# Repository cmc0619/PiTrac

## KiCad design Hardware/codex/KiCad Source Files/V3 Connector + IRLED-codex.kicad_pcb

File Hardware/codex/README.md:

# V3 hardware: Codex variant

This revision starts from PiTracLM/PiTrac `78f1de60fd21398f34d348f19f55e73029bc95f9` and makes three physical corrections. It retains the original architecture and populated parts except for R5's resistance value.

| Change | Reason and effect |
| --- | --- |
| R5: 2.49 kOhm to 6.8 kOhm, `MFR-25FTE52-6K8` | The green supply indicator's original 0.25 W resistor dissipates approximately 0.450 W at the nominal 35.57 V rail. The replacement dissipates approximately 0.165 W and reduces rail load by about 0.303 W. The green indicator is dimmer; the IR LED current-setting network is unchanged. |
| J2/J5 USB4085 power-contact copper | The original front/inner copper diameter was 0.10 mm around a 0.40 mm plated drill. The corrected 0.68 mm land gives a nominal 0.14 mm annular ring. Bottom solder lands are extended to surround the same drills; the local thermal gap is 0.20 mm. |
| D6-D15 center anode connections | The VSMA1085400 center contact is an anode. It is now connected to each LED's existing anode net with a 2.8 x 0.4 mm copper bridge. The bridge stays under solder mask; existing paste and mask openings are unchanged. |

Every existing component position and orientation, mounting hole, drilled pad, via, outline, and 3D model placement is preserved. Existing cases and printed-part geometry are unchanged. Software, the DAC setting/scale, boost current-limit resistor, LED current-setting network and pulse timing are unchanged. No new fuse, TVS, pulse limiter, or USB power-delivery controller is added.

Project-local library tables and project-specific transistor/LED symbols preserve the actual upstream pin definitions when the project is opened on another computer. Intentional unconnected pins, power sources and breakaway holes are identified explicitly. The connector-only board now has its own project file with the same fabrication rules as the combined board.

This directory contains the separately named `-codex` variant. The existing hardware files elsewhere under `Hardware/` remain the Claude/main variant, unchanged. Open `KiCad Source Files/V3 Connector + IRLED-codex.kicad_pro` for this design. The connector-only and LED-only projects are PCB variants; the combined project contains the complete schematic.

## Files to use

- `KiCad Source Files/`: native KiCad 9 schematics, project files, boards and local libraries. KiCad 10 can also read/check these files.
- `Fabrication Files/`: regenerated Gerber and separate plated/nonplated drill ZIPs for all three board variants. Export filenames retain `IRLED2` where applicable and append `-codex`. Internal fabrication filenames use the suffixed PCB project names.
- `Assembly Files/`: regenerated BOMs and centroids. Reference sets and placement coordinates are unchanged; R5 is the only changed ordered part.
- `Schematic/V3 Connector + IRLED2 Schematic-codex.pdf`: regenerated complete schematic.
- `Validation/upstream-iteration/`: verification summary and focused resistor calculation/SPICE evidence.

U4 and C13 remain **do not populate**, as in upstream. They are omitted from the assembly files. With U4 absent, R11 already pulls the MCP4801 shutdown pin high; no DAC modification is needed.

Custom libraries use the `Pi Connector Parts-codex` namespace. The corrected USB4085 and VSMA1085400 footprints also have `-codex` item names. Manufacturer part numbers, schematic values and reference designators are unchanged by naming.

## Verification

KiCad 9.0.8 checks all three boards with zero DRC errors and zero unconnected copper items. The full schematic has zero active ERC violations and two documented, narrowly scoped exceptions: the MC33063 switch emitter tied to ground and the MCP1407's internally connected output pins tied together. No global rule severities were relaxed.

KiCad 10.0.6 independently checks the combined board and full schematic with the same zero-error result. Residual warnings are reported explicitly:

- Each connector board has 16 footprint-library mismatch warnings: 14 standard-footprint differences and two USB instance/library differences. The LED-only board has none.
- Combined-board schematic parity reports 18 unused USB signal pins without copper pads. These dedicated power-only footprints retain those unused contacts as unplated holes, as upstream.
- KiCad 10 additionally reports 32 legacy empty-versus-`~` Datasheet-field differences. These do not change components or connections.

Independent checks compare the original and final netlists, native pad assignments, tracks/vias, holes, outlines, component placements, DNP flags and assembly data. Original pin connectivity is unchanged apart from the ten intended center-anode additions. A separate reviewer found no material introduced defect in the reviewed design at `269b162`. `Validation/naming-codex.json` records the subsequent naming-only checks. The evidence in `Validation/upstream-iteration/` retains its original pre-rename filenames and provenance.

The focused ngspice calculation models only the indicator branch, using a nominal 2.1 V LED drop. Its results agree with resistor-power arithmetic. A conservative 38 V/zero-LED-drop bound including resistor tolerance and temperature coefficient gives approximately 0.215 W for the replacement, below its 0.25 W rating through 70 C local ambient. Higher-temperature operation requires the manufacturer's derating curve and actual conditions.

## Boundaries

These checks establish CAD consistency and the stated electrical calculations. They do not establish measured light output, enclosure temperature, solder yield or physical fit of a populated assembly.

The existing MC33063 charging-current limit remains a separate issue: its 0.15 Ohm sense resistor implies a nominal 2 A threshold, above the controller's 1.5 A switch rating. A lower limit changes reservoir recharge; this revision does not claim to resolve it while preserving the complete strobe/calibration operating envelope. The actual calibration pulse includes software/SPI overhead, so its duration cannot be inferred solely from the SPI wire time.

J2/J5 remain dedicated Pi5 power outputs without USB PD negotiation. Adding ordinary Type-C source resistors would not establish 5 A PD capability. The existing Pi5 supply configuration and upstream current requirements still apply.

## Manufacturer references

- [Yageo MFR resistor ratings, dimensions and ordering](https://yageogroup.com/content/Resource%20Library/Datasheet/YAGEO-MFR_DATASHEET.pdf)
- [Vishay VSMA1085400 package and recommended copper, page 6](https://www.vishay.com/docs/80294/vsma1085400.pdf)
- [GCT USB4085 connector](https://gct.co/connector/usb4085)
- [TI MC33063A controller](https://www.ti.com/lit/ds/symlink/mc33063a.pdf)
- [Microchip MCP1406/1407 output-pin description](https://ww1.microchip.com/downloads/en/DeviceDoc/20002019C.pdf)
- [Raspberry Pi 5 USB Power Delivery](https://pip-assets.raspberrypi.com/categories/685-app-notes-guides-whitepapers/documents/RP-009856-WP-1-USB%20Power%20delivery%20on%20Raspberry%20Pi%205.pdf)

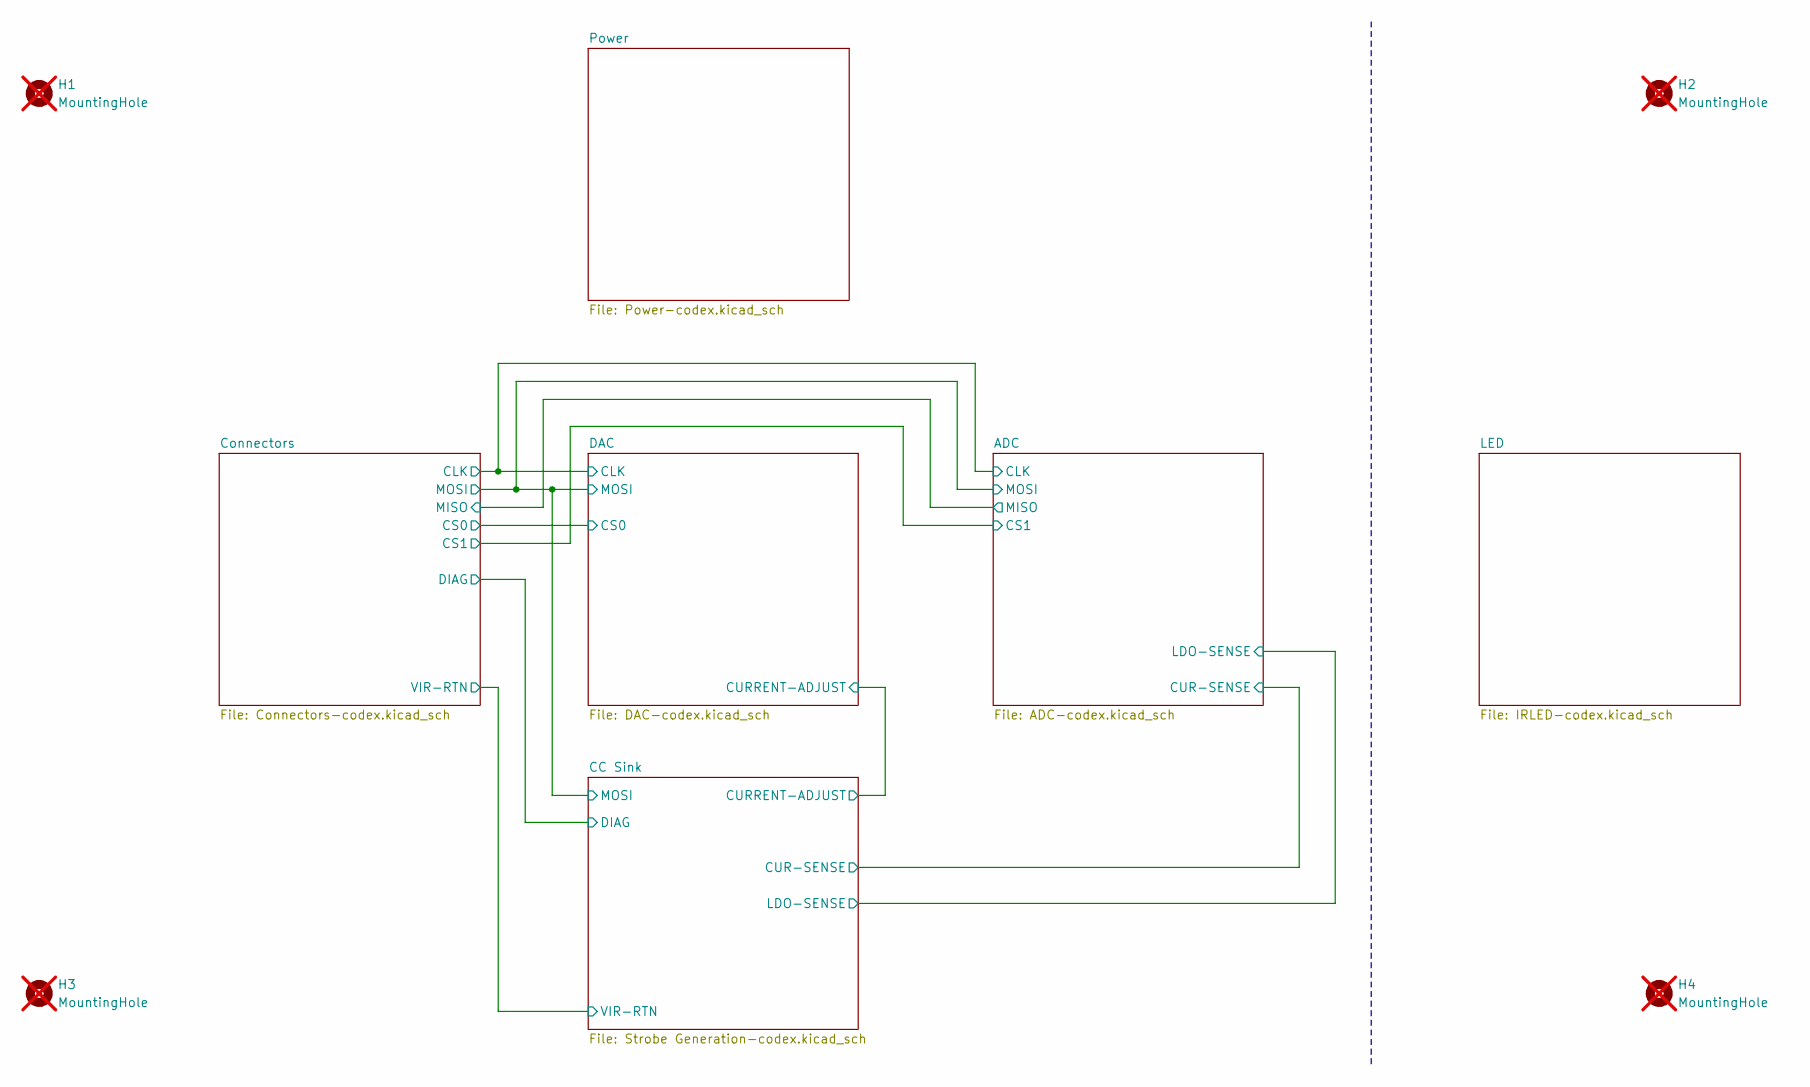
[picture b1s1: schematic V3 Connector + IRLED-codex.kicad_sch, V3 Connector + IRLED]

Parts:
H1, H2, H3, H4: MountingHole; MountingHole_3.5mm; not fitted

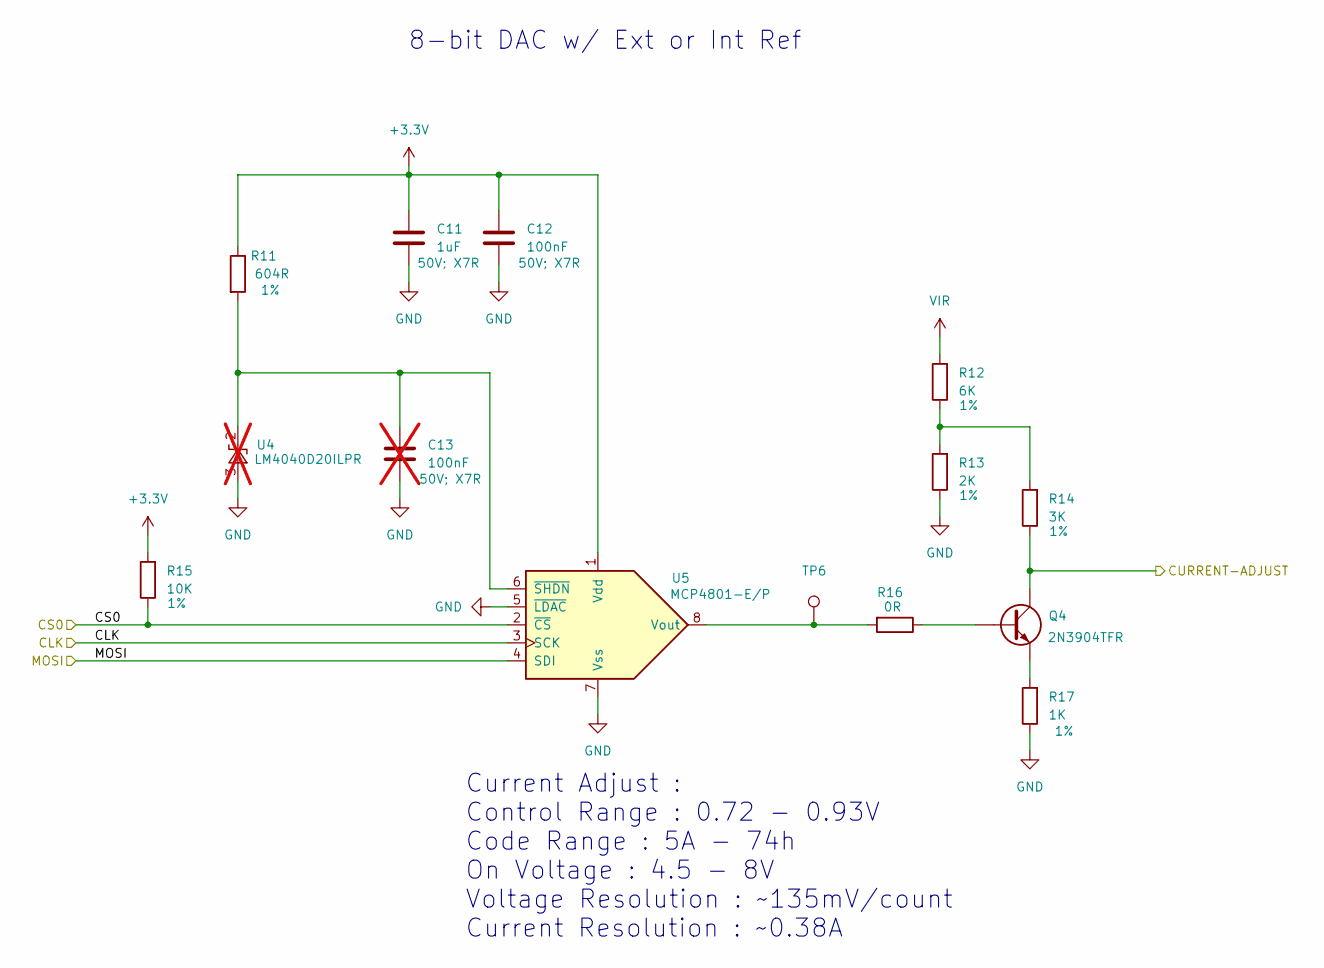
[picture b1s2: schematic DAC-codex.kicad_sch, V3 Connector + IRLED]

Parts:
C11: 1uF; C_Disc_D5.1mm_W3.2mm_P5.00mm; Ratings 50V; X7R; Part Number K105K20X7RF5TH5
C12: 100nF; C_Disc_D4.3mm_W1.9mm_P5.00mm; Ratings 50V; X7R; Part Number K104K10X7RF5UH5
C13: 100nF; C_Disc_D4.3mm_W1.9mm_P5.00mm; Ratings 50V; X7R; Part Number K104K10X7RF5UH5; not fitted
Q4: TO-92_Inline_Wide; Part Number 2N3904TFR
R11: 604R; R_Axial_DIN0207_L6.3mm_D2.5mm_P7.62mm_Horizontal; Ratings 1%; Part Number MFR-25FRF52-604R
R12: 6K; R_Axial_DIN0207_L6.3mm_D2.5mm_P7.62mm_Horizontal; Ratings 1%; Part Number MFR-25FBF52-6K04
R13: 2K; R_Axial_DIN0207_L6.3mm_D2.5mm_P7.62mm_Horizontal; Ratings 1%; Part Number MFR-25FRF52-2K
R14: 3K; R_Axial_DIN0207_L6.3mm_D2.5mm_P7.62mm_Horizontal; Ratings 1%; Part Number MFR-25FRF52-3K
R15: 10K; R_Axial_DIN0207_L6.3mm_D2.5mm_P15.24mm_Horizontal; Ratings 1%; Part Number MFR-25FRF52-10K
R16: 0R; R_Axial_DIN0207_L6.3mm_D2.5mm_P7.62mm_Horizontal; Part Number ZOR-25-R-52-0R
R17: 1K; R_Axial_DIN0207_L6.3mm_D2.5mm_P7.62mm_Horizontal; Ratings 1%; Part Number MFR-25FRF52-1K
TP6: TestPoint; TestPoint_Pad_D1.0mm
U4: LM4040LP-2.0; TO-92_Inline_Wide; Part Number LM4040D20ILPR; not fitted
U5: MCP4801; DIP-8_W7.62mm; Part Number MCP4801-E/P

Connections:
+3.3V: C11.1, C12.1, R11.1, R15.2, U5.1 (Vdd); also elsewhere on the board
/ADC/CLK: U5.3 (SCK); also elsewhere on the board
/ADC/MOSI: U5.4 (SDI); also elsewhere on the board
/CC Sink/CURRENT-ADJUST: Q4.3 (C), R14.1; also elsewhere on the board
/Connectors/CS0: R15.1, U5.2 (~CS); also elsewhere on the board
GND: C11.2, C12.2, C13.2, R13.1, R17.1, U4.3 (A), U5.5 (~LDAC), U5.7 (Vss); also elsewhere on the board
unnamed: Q4.2 (B), R16.1
unnamed: Q4.1 (E), R17.2
unnamed: R12.1, R13.2, R14.2
unnamed: C13.1, R11.2, U4.2 (K), U5.6 (~SHDN)
unnamed: R16.2, TP6.1, U5.8 (Vout)
VIR: R12.2; also elsewhere on the board

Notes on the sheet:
Current Adjust : Control Range : 0.72 - 0.93V Code Range : 5A - 74h On Voltage : 4.5 - 8V Voltage Resolution : ~135mV/count Current Resolution : ~0.38A
8-bit DAC w/ Ext or Int Ref

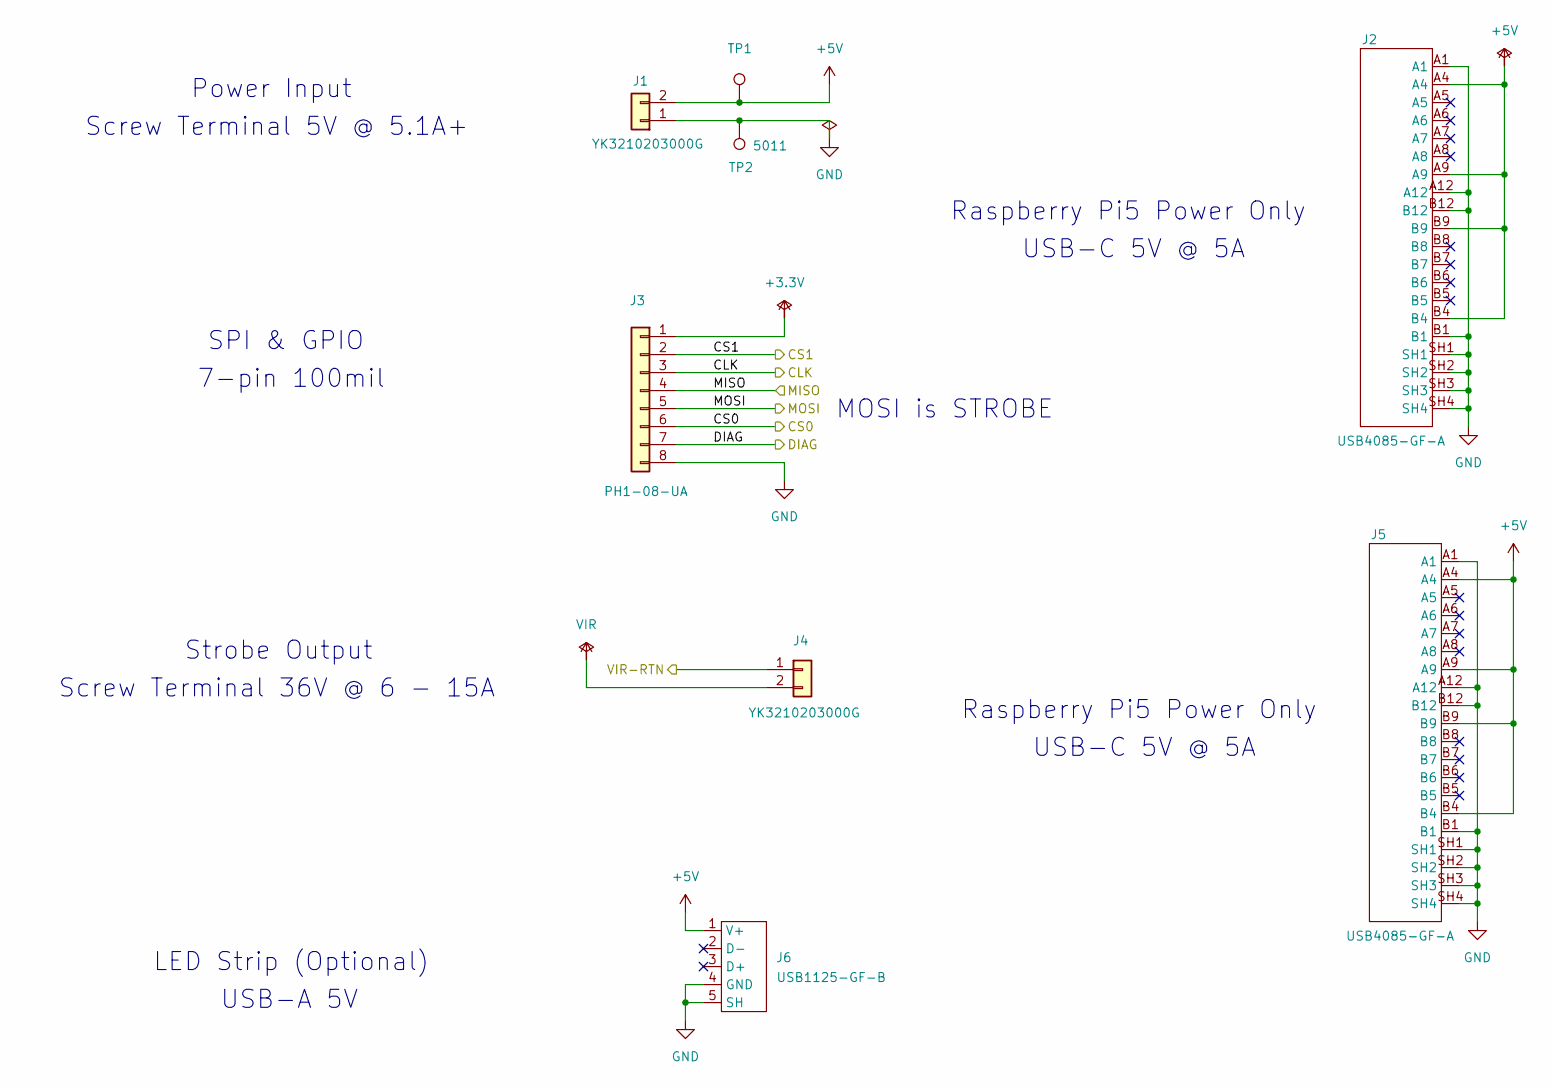
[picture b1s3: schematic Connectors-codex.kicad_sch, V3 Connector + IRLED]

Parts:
J1, J4: YK3210203000G; Part Number YK3210203000G
J2, J5: USB4085-GF-A; USB4085-GF-A-codex; Part Number USB4085-GF-A
J3: Conn_01x08; PinHeader_1x08_P2.54mm_Vertical; Part Number PH1-08-UA
J6: USB1125-GF-B; Part Number USB1125-GF-B
TP1: TestPoint; TestPoint_Pad_D1.0mm
TP2: TestPoint; TestPoint_Keystone_5010-5014_Multipurpose; Part Number 5011

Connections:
+3.3V: J3.1; also elsewhere on the board
+5V: J1.2, J2.A4, J2.A9, J2.B4, J2.B9, J5.A4, J5.A9, J5.B4, J5.B9, J6.1 (V+), TP1.1; also elsewhere on the board
/ADC/CLK: J3.3; also elsewhere on the board
/ADC/CS1: J3.2; also elsewhere on the board
/ADC/MISO: J3.4; also elsewhere on the board
/ADC/MOSI: J3.5; also elsewhere on the board
/CC Sink/DIAG: J3.7; also elsewhere on the board
/CC Sink/VIR-RTN: J4.1; also elsewhere on the board
/Connectors/CS0: J3.6; also elsewhere on the board
GND: J1.1, J2.A1, J2.A12, J2.B1, J2.B12, J2.SH1, J2.SH2, J2.SH3, J2.SH4, J3.8, J5.A1, J5.A12, J5.B1, J5.B12, J5.SH1, J5.SH2, J5.SH3, J5.SH4, J6.4 (GND), J6.5 (SH), TP2.1; also elsewhere on the board
VIR: J4.2; also elsewhere on the board

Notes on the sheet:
Power Input
Raspberry Pi5 Power Only
LED Strip (Optional)
Screw Terminal 36V @ 6 - 15A
MOSI is STROBE
7-pin 100mil
USB-C 5V @ 5A
Screw Terminal 5V @ 5.1A+
USB-A 5V
Strobe Output
SPI & GPIO

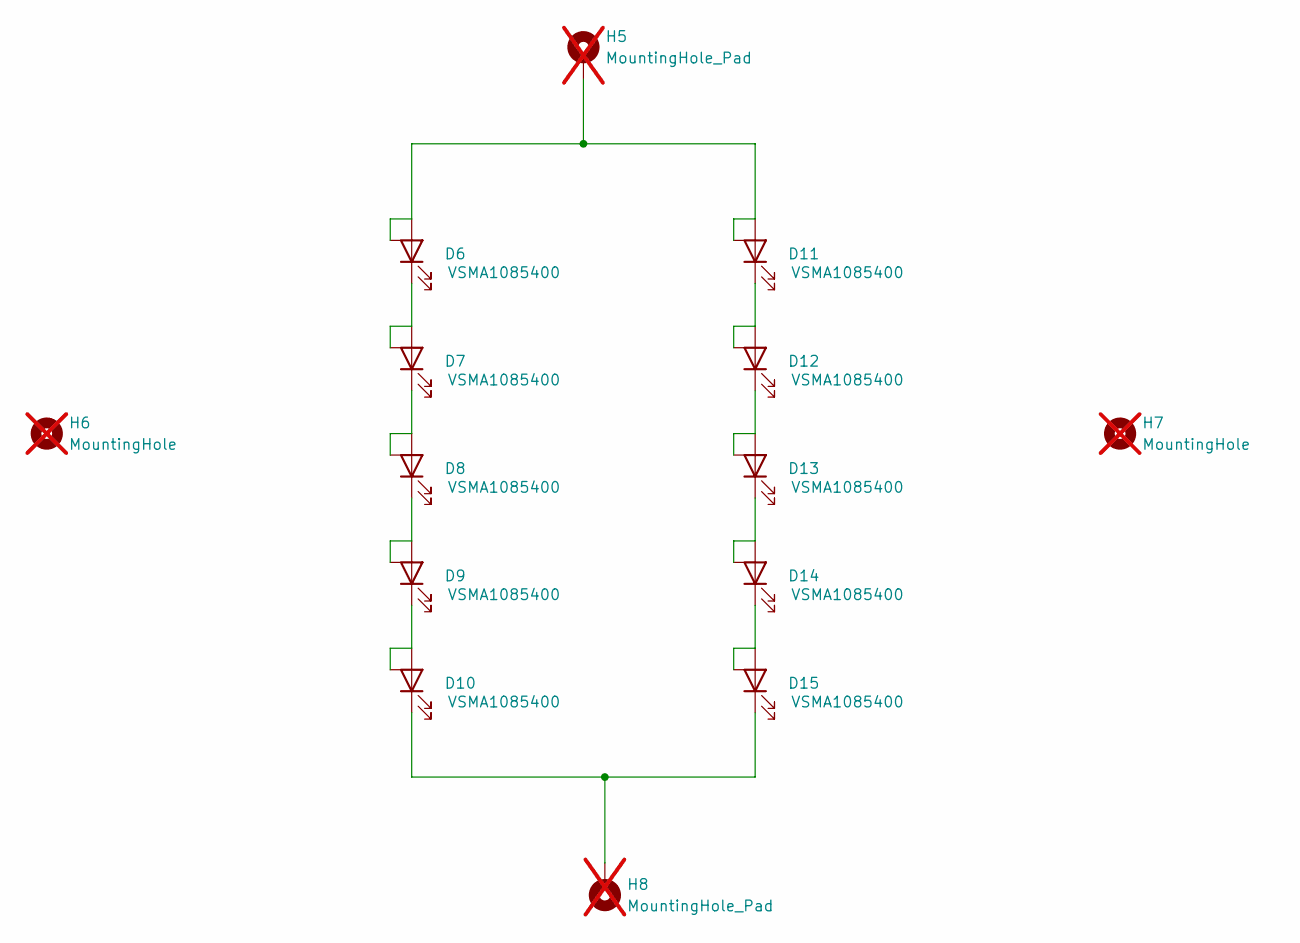
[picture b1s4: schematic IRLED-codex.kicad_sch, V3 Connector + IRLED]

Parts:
D6, D7, D8, D9, D10, D11, D12, D13, D14, D15: VSMA1085400; VSMA1085400-codex; Part Number VSMA1085400
H5, H8: MountingHole_Pad; MountingHole_2.2mm_M2_Pad; not fitted
H6, H7: MountingHole; MountingHole_3.2mm_M3; not fitted

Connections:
unnamed: D6.1 (K), D7.2 (A), D7.3
unnamed: D7.1 (K), D8.2 (A), D8.3
unnamed: D8.1 (K), D9.2 (A), D9.3
unnamed: D9.1 (K), D10.2 (A), D10.3
unnamed: D10.1 (K), D15.1 (K), H8.1
unnamed: D6.2 (A), D6.3, D11.2 (A), D11.3, H5.1
unnamed: D11.1 (K), D12.2 (A), D12.3
unnamed: D12.1 (K), D13.2 (A), D13.3
unnamed: D13.1 (K), D14.2 (A), D14.3
unnamed: D14.1 (K), D15.2 (A), D15.3

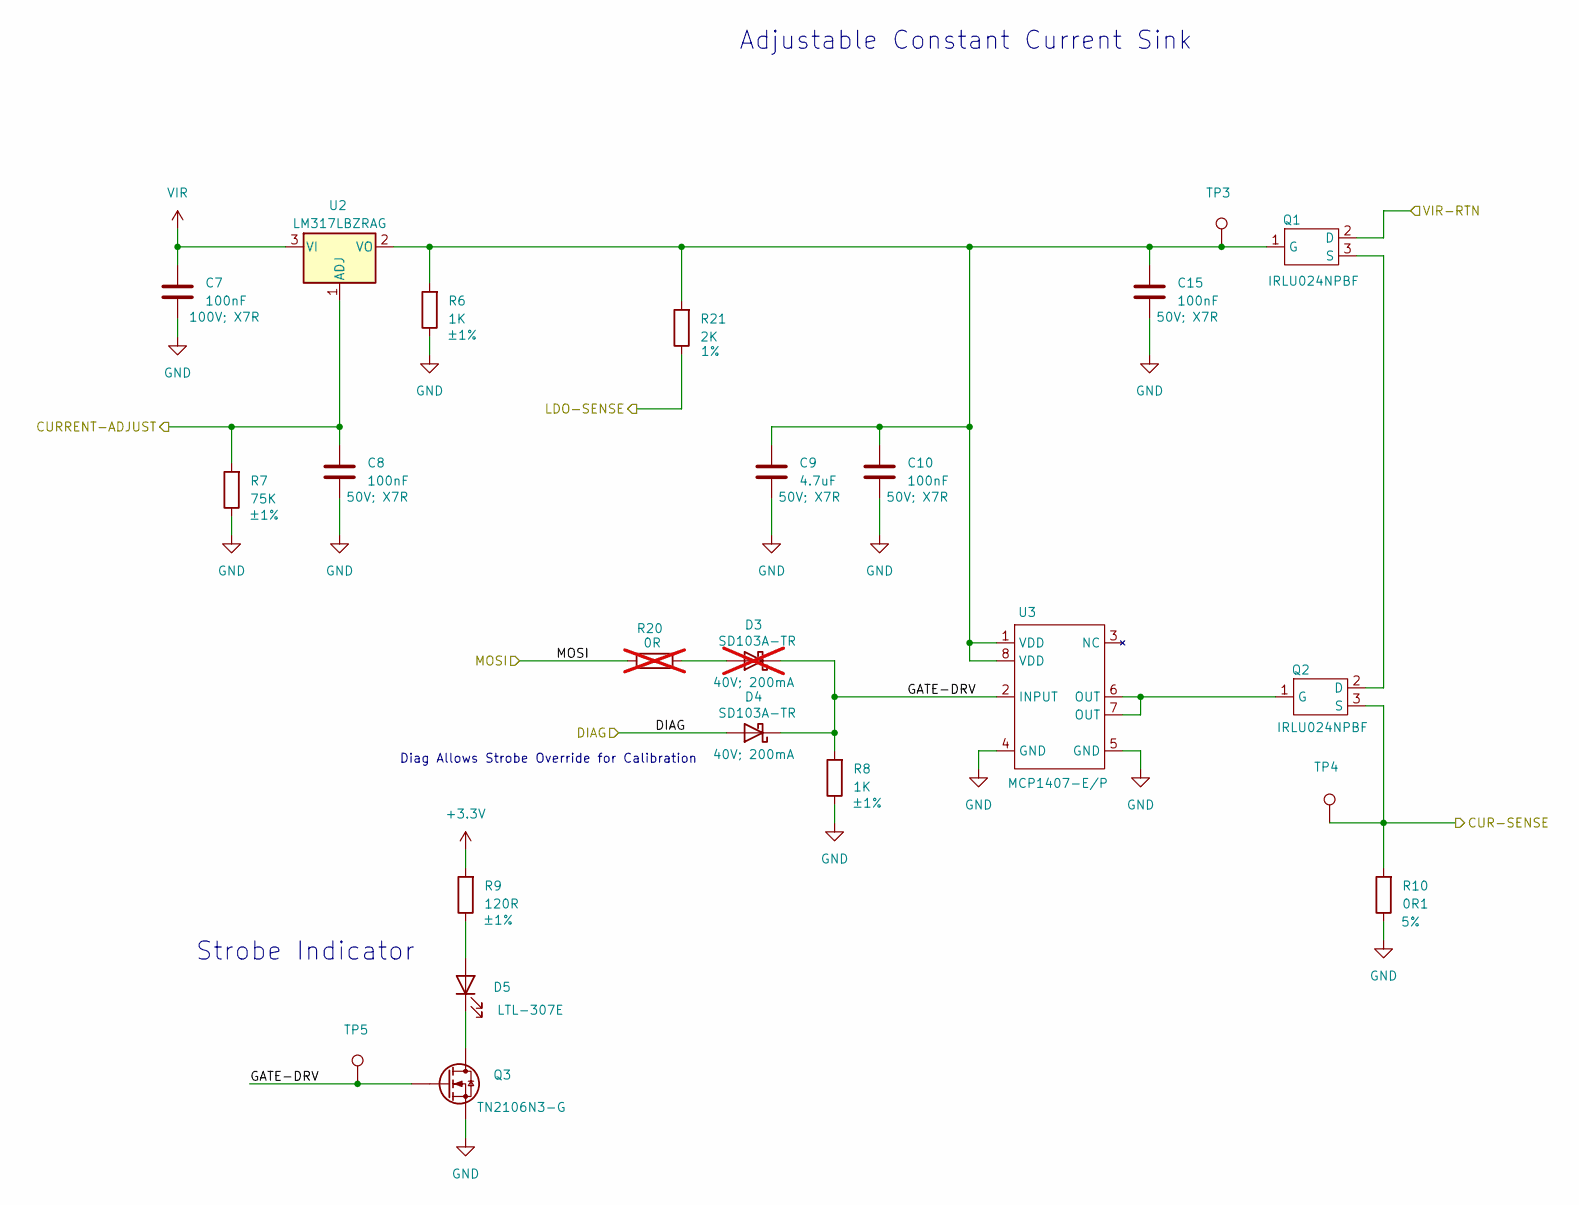
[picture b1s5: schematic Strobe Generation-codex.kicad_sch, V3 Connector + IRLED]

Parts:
C7: 100nF; C_Disc_D5.1mm_W3.2mm_P5.00mm; Ratings 100V; X7R; Part Number K104K20X7RH5UH5
C8, C10, C15: 100nF; C_Disc_D4.3mm_W1.9mm_P5.00mm; Ratings 50V; X7R; Part Number K104K10X7RF5UH5
C9: 4.7uF; C_Disc_D6.0mm_W4.4mm_P5.00mm; Ratings 50V; X7R; Part Number RCER71H475K3K1H03B
D3: D_Schottky; D_DO-35_SOD27_P7.62mm_Horizontal; Ratings 40V; 200mA; Part Number SD103A-TR; not fitted
D4: D_Schottky; D_DO-35_SOD27_P7.62mm_Horizontal; Ratings 40V; 200mA; Part Number SD103A-TR
D5: LTL-307E; LED_D5.0mm; Part Number LTL-307E
Q1, Q2: IRLU024NPBF; TO-251-3_Vertical; Part Number IRLU024NPBF
Q3: Q_NMOS; TO-92_Inline_Wide; Part Number TN2106N3-G
R6, R8: 1K; R_Axial_DIN0207_L6.3mm_D2.5mm_P7.62mm_Horizontal; Ratings ±1%; Part Number MFR-25FRF52-1K
R7: 75K; R_Axial_DIN0207_L6.3mm_D2.5mm_P7.62mm_Horizontal; Ratings ±1%; Part Number MFR-25FRF52-75K
R9: 120R; R_Axial_DIN0207_L6.3mm_D2.5mm_P7.62mm_Horizontal; Ratings ±1%; Part Number MFR-25FTE52-120R
R10: 0R1; R_Axial_DIN0414_L11.9mm_D4.5mm_P15.24mm_Horizontal; Ratings 5%; Part Number KNP100JR-73-0R1
R20: 0R; R_Axial_DIN0207_L6.3mm_D2.5mm_P7.62mm_Horizontal; Part Number ZOR-25-R-52-0R; not fitted
R21: 2K; R_Axial_DIN0207_L6.3mm_D2.5mm_P7.62mm_Horizontal; Ratings 1%; Part Number MFR-25FRF52-2K
TP3, TP4, TP5: TestPoint; TestPoint_Pad_D1.0mm
U2: TO-92_Inline_Wide; Part Number LM317LBZRAG
U3: DIP-8_W7.62mm; Part Number MCP1407-E/P

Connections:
+3.3V: R9.2; also elsewhere on the board
/ADC/CUR-SENSE: Q2.3 (S), R10.2, TP4.1; also elsewhere on the board
/ADC/LDO-SENSE: R21.1; also elsewhere on the board
/ADC/MOSI: R20.2; also elsewhere on the board
/CC Sink/CURRENT-ADJUST: C8.1, R7.2, U2.1 (ADJ); also elsewhere on the board
/CC Sink/DIAG: D4.2 (A); also elsewhere on the board
/CC Sink/GATE-DRV: D3.1 (K), D4.1 (K), Q3.2, R8.2, TP5.1, U3.2 (INPUT)
/CC Sink/VIR-RTN: Q1.2 (D); also elsewhere on the board
GND: C7.2, C8.2, C9.2, C10.2, C15.2, Q3.1, R6.1, R7.1, R8.1, R10.1, U3.4 (GND), U3.5 (GND); also elsewhere on the board
unnamed: D3.2 (A), R20.1
unnamed: D5.2 (A), R9.1
unnamed: D5.1 (K), Q3.3
unnamed: C9.1, C10.1, C15.1, Q1.1 (G), R6.2, R21.2, TP3.1, U2.2 (VO), U3.1 (VDD), U3.8 (VDD)
unnamed: Q1.3 (S), Q2.2 (D)
unnamed: Q2.1 (G), U3.6 (OUT), U3.7 (OUT)
VIR: C7.1, U2.3 (VI); also elsewhere on the board

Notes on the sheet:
Diag Allows Strobe Override for Calibration
Adjustable Constant Current Sink
Strobe Indicator

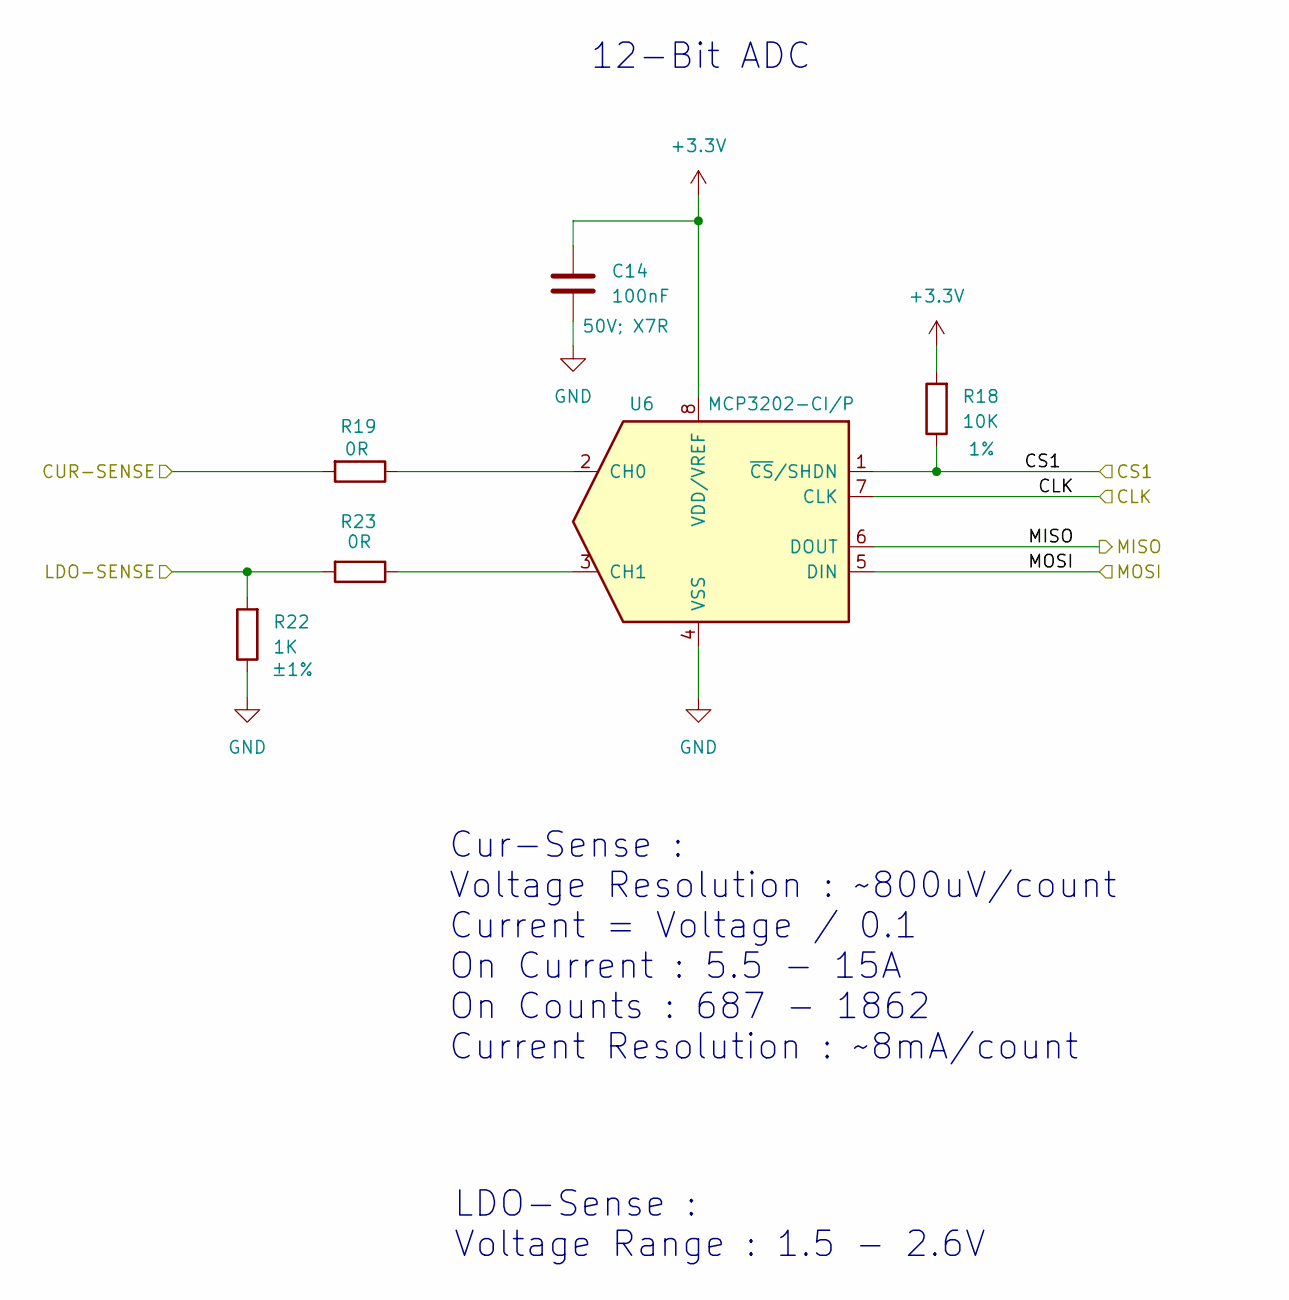
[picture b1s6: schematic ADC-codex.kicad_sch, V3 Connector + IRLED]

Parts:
C14: 100nF; C_Disc_D4.3mm_W1.9mm_P5.00mm; Ratings 50V; X7R; Part Number K104K10X7RF5UH5
R18: 10K; R_Axial_DIN0207_L6.3mm_D2.5mm_P7.62mm_Horizontal; Ratings 1%; Part Number MFR-25FRF52-10K
R19, R23: 0R; R_Axial_DIN0207_L6.3mm_D2.5mm_P15.24mm_Horizontal; Part Number ZOR-25-R-52-0R
R22: 1K; R_Axial_DIN0207_L6.3mm_D2.5mm_P7.62mm_Horizontal; Ratings ±1%; Part Number MFR-25FRF52-1K
U6: MCP3202; DIP-8_W7.62mm; Part Number MCP3202-CI/P

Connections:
+3.3V: C14.1, R18.2, U6.8 (VDD/VREF); also elsewhere on the board
/ADC/CLK: U6.7 (CLK); also elsewhere on the board
/ADC/CS1: R18.1, U6.1 (~CS/SHDN); also elsewhere on the board
/ADC/CUR-SENSE: R19.2; also elsewhere on the board
/ADC/LDO-SENSE: R22.2, R23.2; also elsewhere on the board
/ADC/MISO: U6.6 (DOUT); also elsewhere on the board
/ADC/MOSI: U6.5 (DIN); also elsewhere on the board
GND: C14.2, R22.1, U6.4 (VSS); also elsewhere on the board
unnamed: R19.1, U6.2 (CH0)
unnamed: R23.1, U6.3 (CH1)

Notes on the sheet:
Cur-Sense : Voltage Resolution : ~800uV/count Current = Voltage / 0.1 On Current : 5.5 - 15A On Counts : 687 - 1862 Current Resolution : ~8mA/count
LDO-Sense : Voltage Range : 1.5 - 2.6V
12-Bit ADC

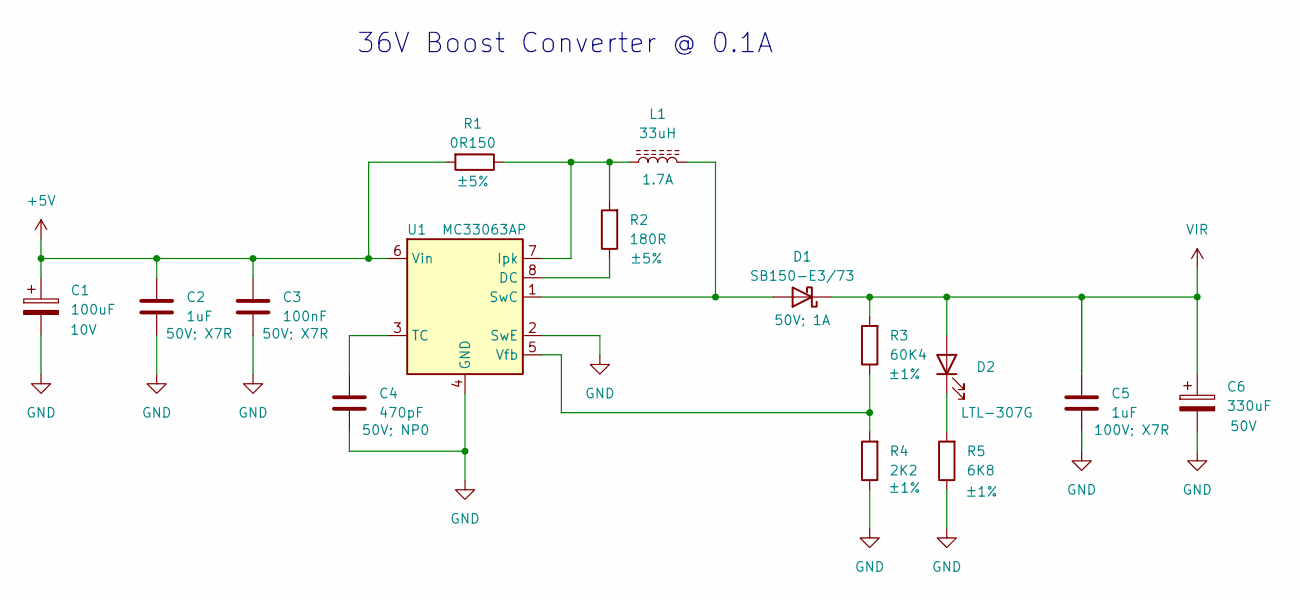
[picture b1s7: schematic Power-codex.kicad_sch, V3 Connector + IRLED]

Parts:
C1: 100uF; CP_Radial_D5.0mm_P2.00mm; Ratings 10V; Part Number A750BK107M1AAAE024
C2: 1uF; C_Disc_D5.1mm_W3.2mm_P5.00mm; Ratings 50V; X7R; Part Number K105K20X7RF5TH5
C3: 100nF; C_Disc_D4.3mm_W1.9mm_P5.00mm; Ratings 50V; X7R; Part Number K104K10X7RF5UH5
C4: 470pF; C_Disc_D4.7mm_W2.5mm_P5.00mm; Ratings 50V; NP0; Part Number K471J15C0GF5UH5
C5: 1uF; C_Disc_D5.1mm_W3.2mm_P5.00mm; Ratings 100V; X7R; Part Number RDER72A105K2M1H03A
C6: 330uF; CP_Radial_D10.0mm_P5.00mm; Ratings 50V; Part Number A750MW337M1HAAE020
D1: SB150-E3/73; D_DO-41_SOD81_P10.16mm_Horizontal; Ratings 50V; 1A; Part Number SB150-E3/73
D2: LTL-307G; LED_D5.0mm; Part Number LTL-307G
L1: 33uH; L_Radial_D8.7mm_P5.00mm_Fastron_07HCP; Ratings 1.7A; Part Number RLB0914-330KL
R1: 0R150; R_Axial_DIN0516_L15.5mm_D5.0mm_P20.32mm_Horizontal; Ratings ±5%; Part Number PNP300JR-73-0R15
R2: 180R; R_Axial_DIN0207_L6.3mm_D2.5mm_P10.16mm_Horizontal; Ratings ±5%; Part Number KNP1WSJT-52-180R
R3: 60K4; R_Axial_DIN0207_L6.3mm_D2.5mm_P7.62mm_Horizontal; Ratings ±1%; Part Number MFR-25FRF52-60K4
R4: 2K2; R_Axial_DIN0207_L6.3mm_D2.5mm_P7.62mm_Horizontal; Ratings ±1%; Part Number MFR-25FRF52-2K2
R5: 6K8; R_Axial_DIN0207_L6.3mm_D2.5mm_P7.62mm_Horizontal; Ratings ±1%; Part Number MFR-25FTE52-6K8
U1: MC33063AP; DIP-8_W7.62mm; Part Number MC33063AP

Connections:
+5V: C1.1, C2.1, C3.1, R1.2, U1.6 (Vin); also elsewhere on the board
GND: C1.2, C2.2, C3.2, C4.1, C5.2, C6.2, R4.1, R5.1, U1.2 (SwE), U1.4 (GND); also elsewhere on the board
unnamed: D1.2 (A), L1.2, U1.1 (SwC)
unnamed: D2.1 (K), R5.2
unnamed: R2.1, U1.8 (DC)
unnamed: L1.1, R1.1, R2.2, U1.7 (Ipk)
unnamed: C4.2, U1.3 (TC)
unnamed: R3.1, R4.2, U1.5 (Vfb)
VIR: C5.1, C6.1, D1.1 (K), D2.2 (A), R3.2; also elsewhere on the board

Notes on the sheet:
36V Boost Converter @ 0.1A

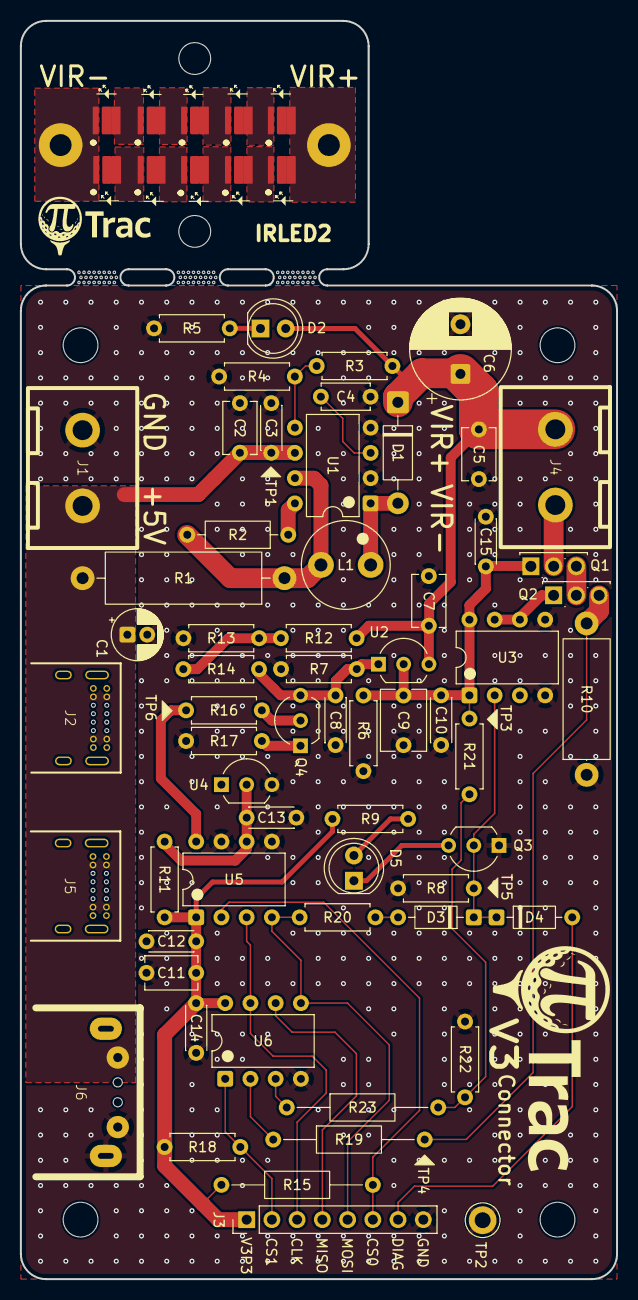
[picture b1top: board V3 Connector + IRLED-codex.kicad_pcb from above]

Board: 2 copper layers, 60.0 x 126.6 mm, 79 parts (0 on the bottom side), 44 nets.
